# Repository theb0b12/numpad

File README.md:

# numpad
This was a late night project.
2 numpads, one normal sized (smallishnum), and one smaller (smallnum)

smallishnum layout

smallnum layout

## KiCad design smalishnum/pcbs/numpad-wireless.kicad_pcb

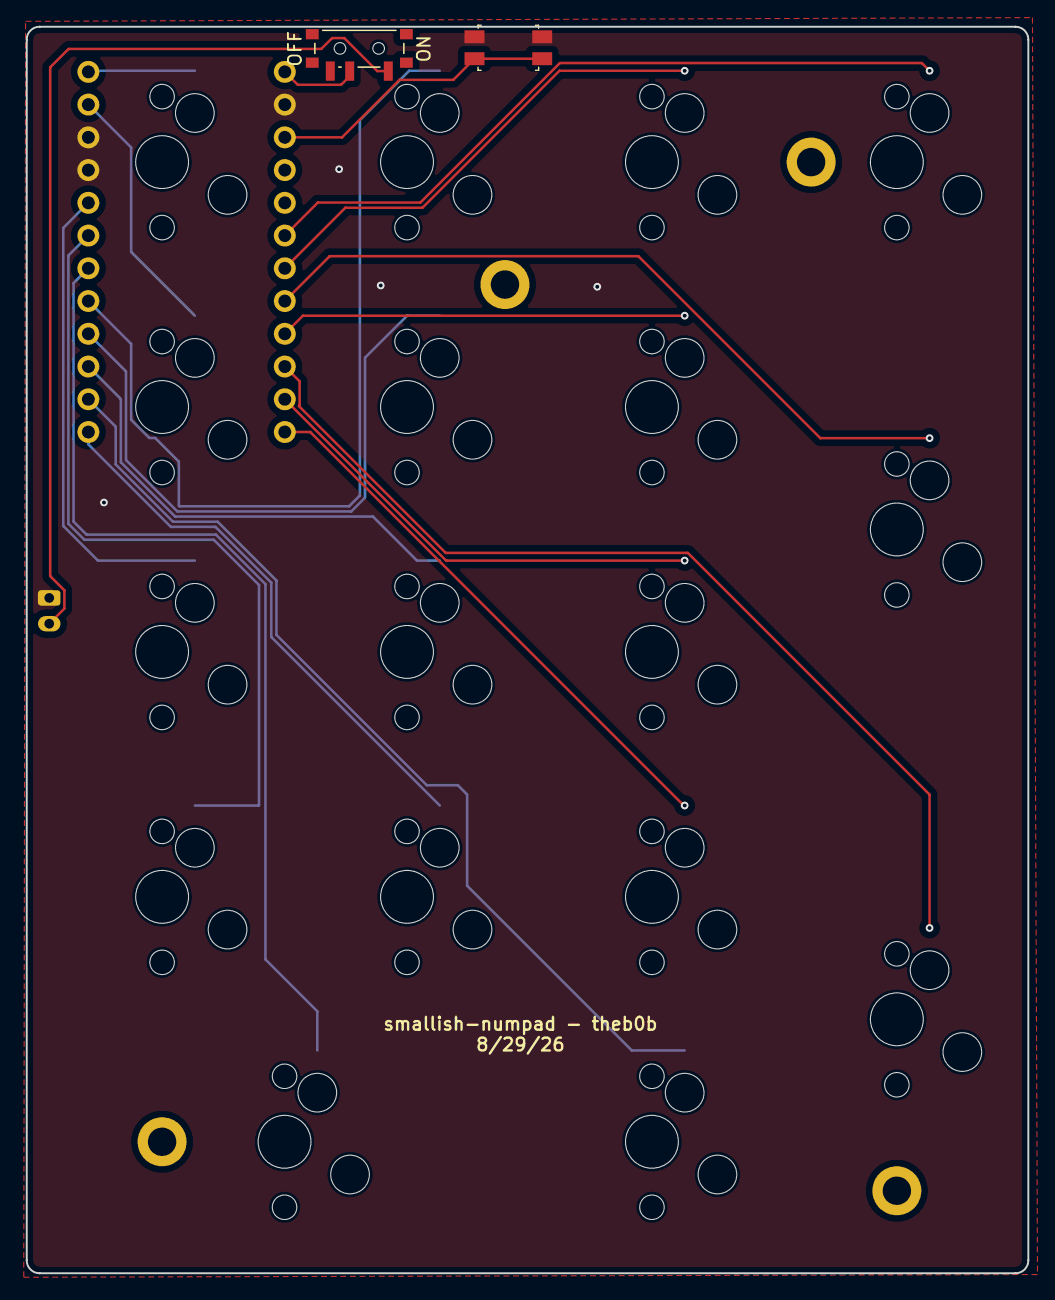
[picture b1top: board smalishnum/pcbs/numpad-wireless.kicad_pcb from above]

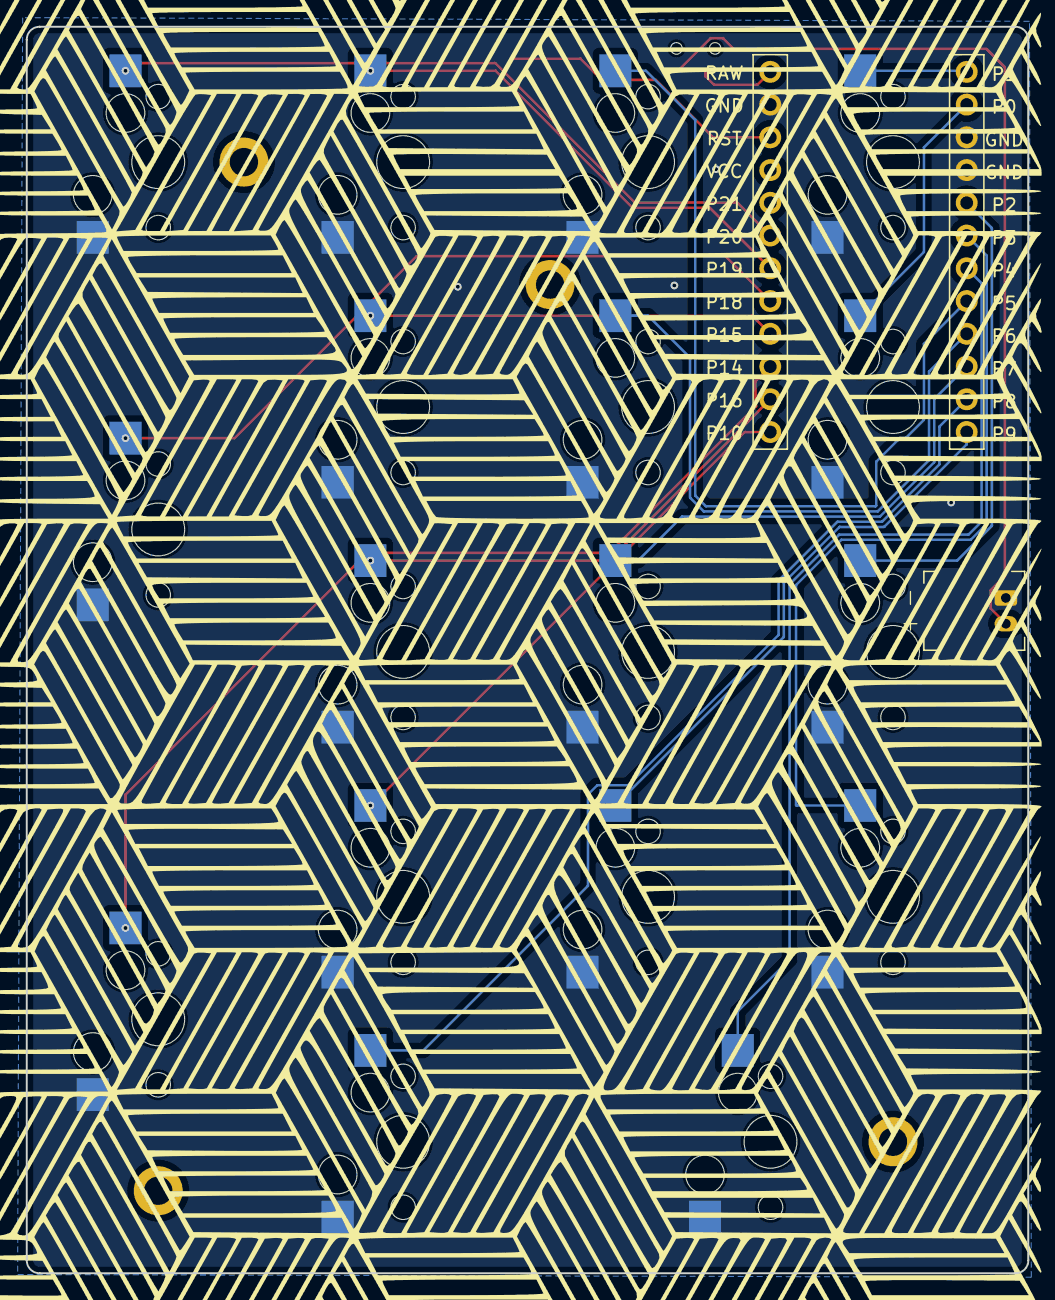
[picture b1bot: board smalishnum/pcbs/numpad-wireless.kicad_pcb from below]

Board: 2 copper layers, 77.7 x 96.7 mm, 25 parts (19 on the bottom side), 21 nets.

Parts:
H1, H2, H3, H4: mounting_hole_plated
JST1: battery_connector_jst_ph_2
MCU1: mcu_nice_nano
PWR1: power_switch_smd_side
RST1: reset_switch_smd_side
S1, S2, S3, S4, S5, S6, S7, S8, S9, S10, S11, S12, S13, S14, S15, S16, S17: switch_mx_noss

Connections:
BAT_P: JST1.2, PWR1.1
GND: JST1.1, MCU1.2, MCU1.21, MCU1.22, RST1.1, RST1.3, S1.2, S2.2, S3.2, S4.2, S5.2, S6.2, S7.2, S8.2, S9.2, S10.2, S11.2, S12.2, S13.2, S14.2, S15.2, S16.2, S17.2
P0: MCU1.23, S4.1
P1: MCU1.24, S5.1
P2: MCU1.20, S3.1
P3: MCU1.19, S2.1
P4: MCU1.18, S1.1
P5: MCU1.17, S9.1
P6: MCU1.16, S8.1
P7: MCU1.15, S7.1
P8: MCU1.14, S10.1
P9: MCU1.13, S6.1
P10: MCU1.12, S11.1
P14: MCU1.10, S15.1
P15: MCU1.9, S13.1
P16: MCU1.11, S12.1
P18: MCU1.8, S16.1
P19: MCU1.7, S14.1
P20: MCU1.6, S17.1
RAW: MCU1.1, PWR1.2
RST: MCU1.3, RST1.2, RST1.4

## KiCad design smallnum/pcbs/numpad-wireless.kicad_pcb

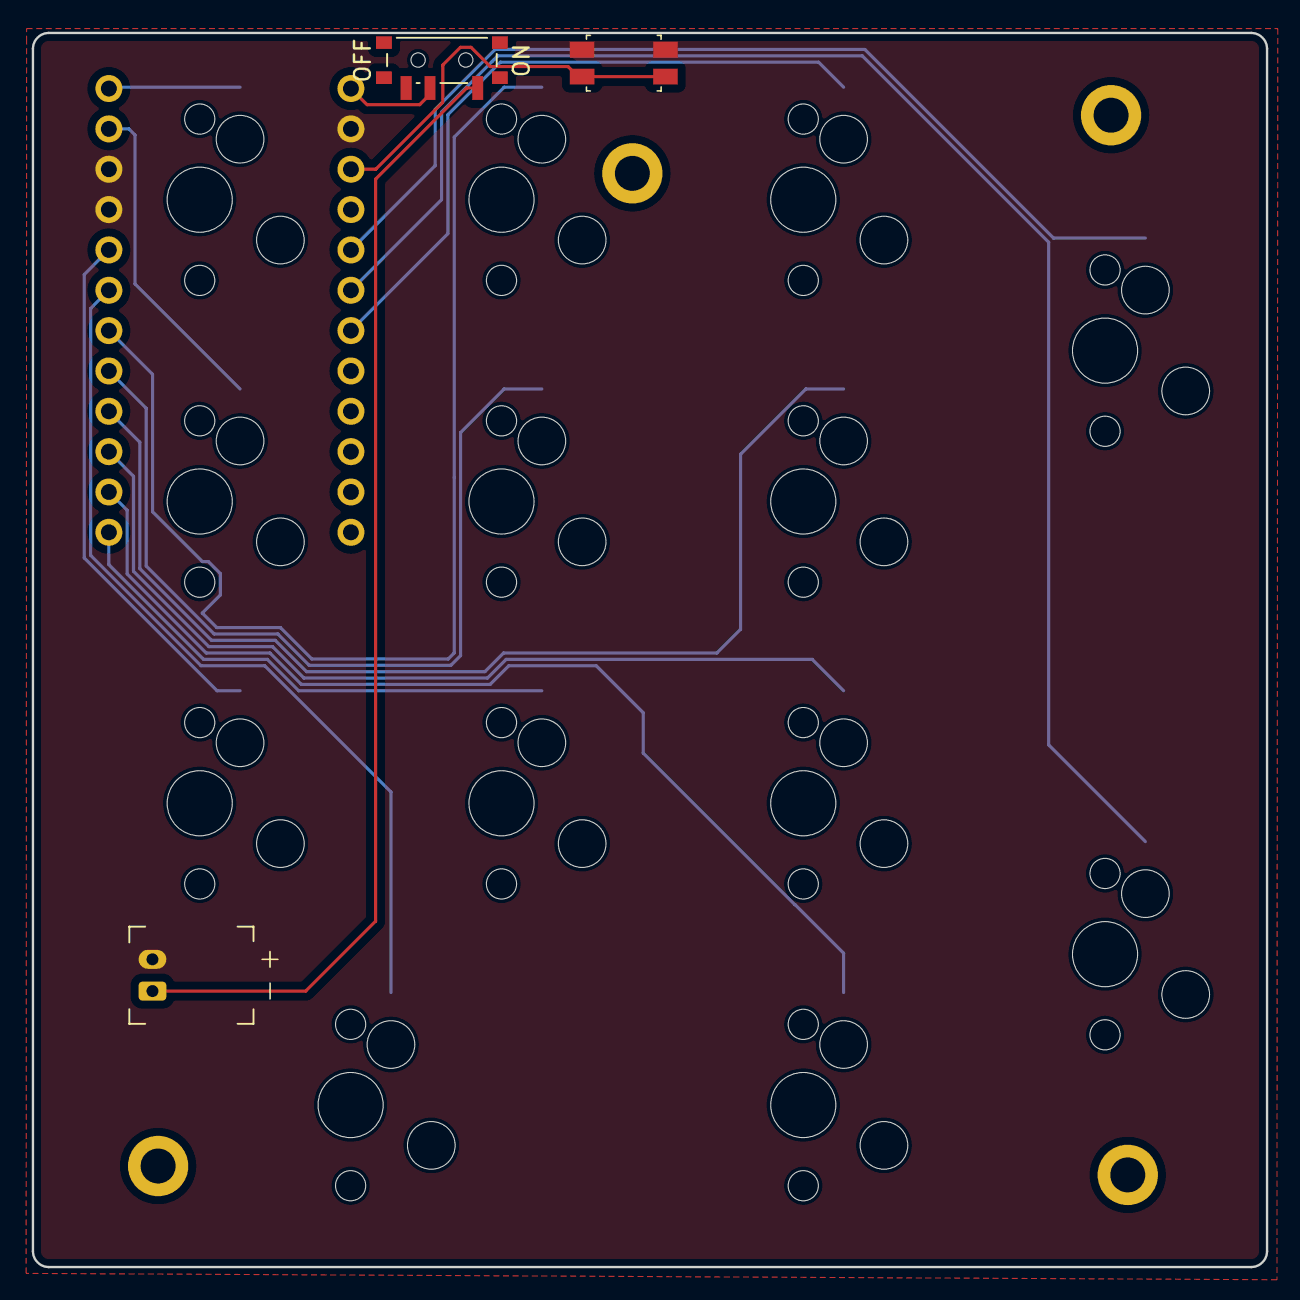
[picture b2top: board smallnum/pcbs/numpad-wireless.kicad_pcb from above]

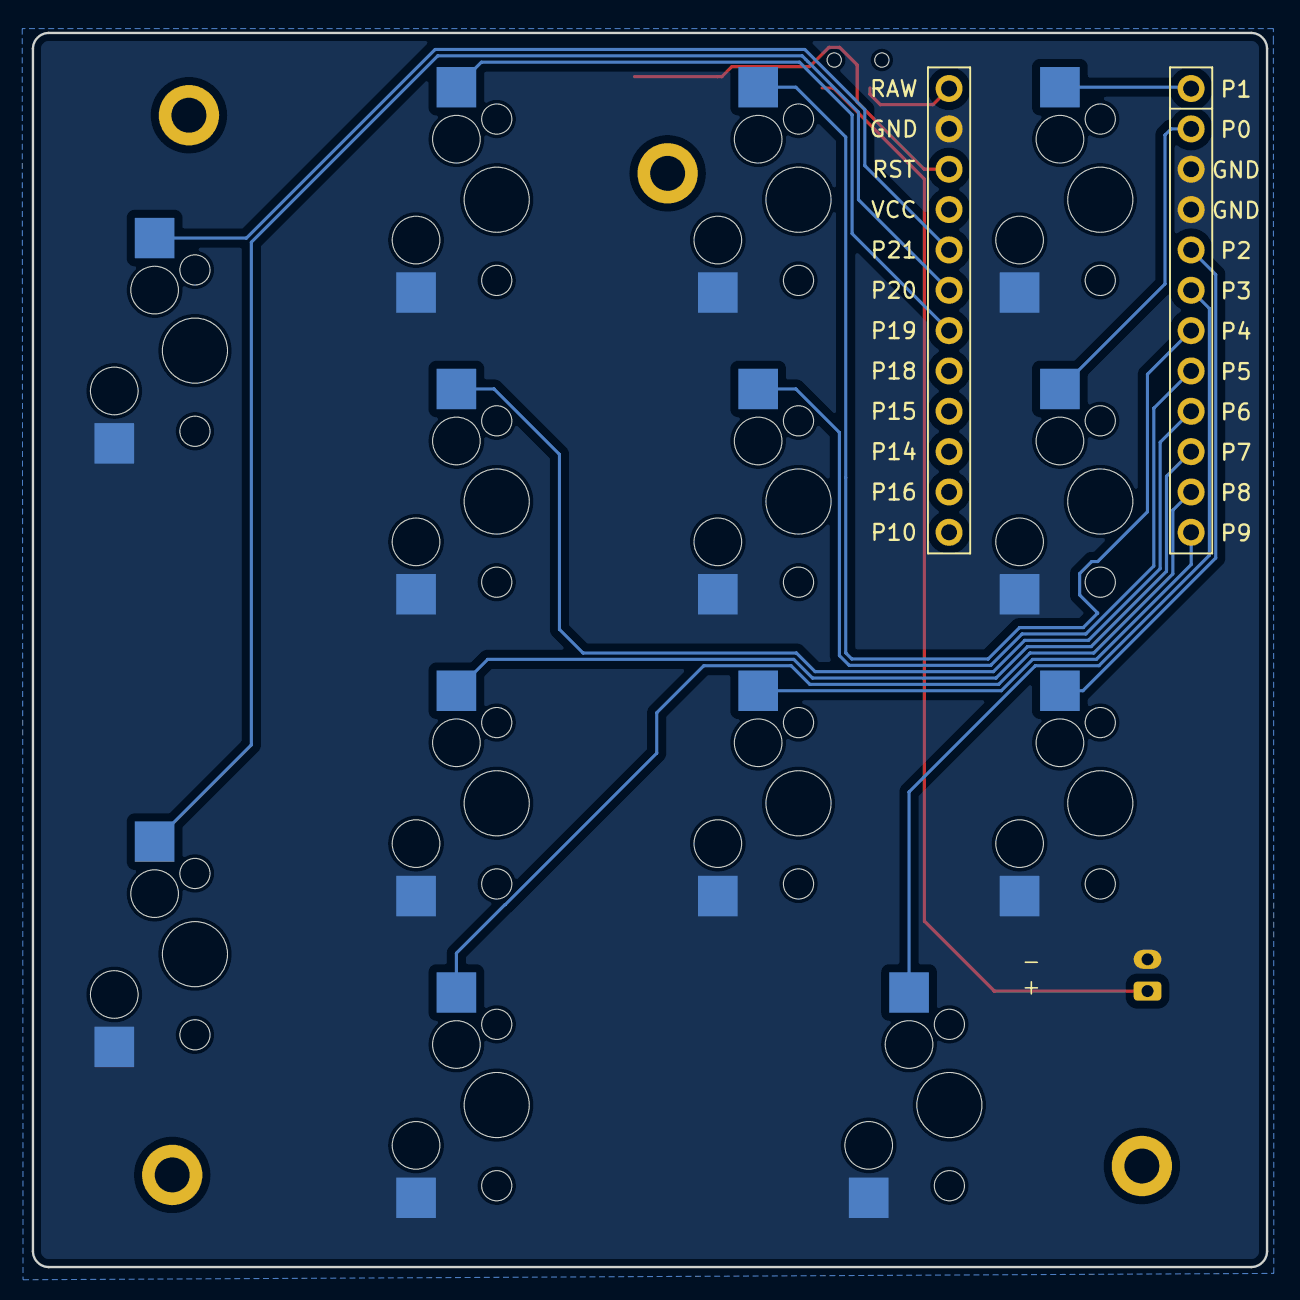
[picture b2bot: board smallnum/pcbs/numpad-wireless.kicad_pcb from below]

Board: 2 copper layers, 77.7 x 77.7 mm, 21 parts (14 on the bottom side), 17 nets.

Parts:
H2, H2#2, H2#3, H2#4: mounting_hole_plated
JST1: battery_connector_jst_ph_2
MCU1: mcu_nice_nano
PWR1: power_switch_smd_side
RST1: reset_switch_smd_side
S1, S2, S3, S4, S5, S6, S7, S8, S9, S10, S11, S12, S13: switch_mx_noss

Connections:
BAT_P: JST1.1, PWR1.1
GND: JST1.2, MCU1.2, MCU1.21, MCU1.22, RST1.1, RST1.3, S1.2, S2.2, S3.2, S4.2, S5.2, S6.2, S7.2, S8.2, S9.2, S10.2, S11.2, S12.2, S13.2
P0: MCU1.23, S3.1
P1: MCU1.24, S4.1
P2: MCU1.20, S2.1
P3: MCU1.19, S1.1
P4: MCU1.18, S7.1
P5: MCU1.17, S6.1
P6: MCU1.16, S10.1
P7: MCU1.15, S9.1
P8: MCU1.14, S8.1
P9: MCU1.13, S5.1
P19: MCU1.7, S11.1
P20: MCU1.6, S12.1
P21: MCU1.5, S13.1
RAW: MCU1.1, PWR1.2
RST: MCU1.3, RST1.2, RST1.4
